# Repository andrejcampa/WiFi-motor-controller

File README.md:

# Wifi motor controller

WiFi motor controller is a highly efficient DC motor controller for creating simple remote controlled toys using a mobile device. The main purpose of the project was to build a simple WiFi controller for N/HO scale trains. However, the motor driver is not limited to trains but can also be efficiently implemented to other simple DIY toys.  The project is divided into three independent and customizable parts: hardware (HW) part, software (SW) part and optional custom 3D printed train. 

Key Specifications:
-	Supply voltage 6-15V (polarity insensitive)
-	Maximum output current 0.5A (BD622OF)/ 1A (BDF6221F)
-	Access point to the device (independent to mobile device system), no external software needed to control the device

 # Contents

- [1. HW Part](#1-hw-part) 
- [2. SW Part](#2-sw-part)
- [3. 3D Printed parts](#3-3d-printed-parts)
- [4. Support](#4-support)

## 1. HW Part

Fig 1.1: The picture of the front and back of the WiFi motor control with dimensions in mm.

The hardware of the controller was created with KiCad EDA; I have been using nightly builds release 5, since it is a huge step forward with features, libraries, etc. There are some inconsistencies between the Linux and Windows version thus you might need to make some slight changes to the naming of parts (for instance in windows the library symbol for a resistor is device:R while in Linux Device:R).
The hardware is based around BD622XF H-bridge driver and the most important features of HW are summarized in the block diagram. The maximal pulse voltage at the motor is equal to the input voltage reduced by the diode bridge voltage drop (~0.5V). Please consider using the power supply voltage of 12V - 15V to maximize the performance of H-bridge, since the module is very small 13.5 mm x 23.8 mm (31 mm) and the current capacity is limited.

Fig. 1.2: Block diagram of the module.

### Interface pins definition and connection

Fig. 1.3: Definition of pins and “connection scheme”.

Pin name | Description
------------ | -------------
**ext C (- +)** | optional external capacitor, beware of the polarity!
**LEDs** | two connections for LEDs, the maximal current is 10 mA limited by 1k resistor, this is FET driven output connected to high voltage Uin and can be used for signaling. Also marked as out 1 and out 2 in the block diagram.
**Motor_DC** | the output for DC motor, polarity and PWM voltage signal is controlled by MUC.
**U 6V-15V** | main input power for the HW and motor, Uin = 6V-15V

### PCB
The latest Gerber for PCB production can be found in the directory HW/gerber/vlak.zip. The compressed archive was already used and sent to one of the cheap Chinese PCB Manufacturer. Please contact me if you need some additional information or how to reduce the costs of a prototype.

## 2. SW part

### Flashing

The main WiFi + MCU unit is based on a small esp8285 module, ESP-M2 (doit.am). Please refer to documentation how to flash the module. You have the option to program the ESP module on the board. However, you have to supply the power to the input pins and additionally solder the ground, Rx and Tx pin directly to the module (see ESP-M2 documentation).  To flash you will need to short and hold flash pads and in the meantime short the reset pads, Figure 2.1. Flash and Reset pads are exposed on the front side of PCB.

Fig. 2.1: Exposed pads for flashing the module.

### Program
The program is written in Arduino IDE, using the open libraries, Arduino core for ESP8266 Wifi chip. To improve the response time I have used an asynchronous web server. The soft access point (SoftAP) is implemented. The program uses for SSID SRS and the serial number (SRS xxxx), the default password is SRS12345 and is for now only changeable from the program. The default page is packed in the header file as the stream of characters (string), so no file system is needed.
To access and to control the module you have to open the web browser after connecting to the hotspot. In the browser you should write the address 192.168.4.1 to access the control panel, Fig 2.2. With the slide bar you can adjust the speed, with the left and right button you can control the direction while the X button will stop the motor. In all cases soft acceleration is adapted to stabilize the module and motor, to have smooth driving experience. On the right side, the two additional buttons for turning LEDs on and off are presented. The program is written for N and HO scale train purposes and can be easily adjusted for other needs by modifying the existing page and program.

Fig. 2.2: Screenshot of UI.

## 3. 3D printed parts
The first 3-D printed locomotive is in directory 3D. You need FreeCAD to open and edit the locomotive hull. The completed locomotive can be seen in the [demonstration video](https://youtu.be/si7zXm7mwlY).

To use the WiFi module with the 3D printed hull you also need Tomytec TM-07R Motorized Chassis (N scale). By connecting the LEDs (3 mm size) and module like in Fig. 1.3 you should get a connection similar as shown in Fig. 3.1. For this project you can use very thin wires 0.05mm2 (30AWG) since the current capacity of such wire is enough for our 0.5A or 1A maximal current.

Fig. 3.1: Assembling the module into the 3D printed hull.

Please contact me if the detailed step by step instructions are needed!

## 4. Support
You are encouraged to support the project in many different ways
1. To track bugs.
2. To improve the SW part with a better response.
3. To create custom control panels in HTML.
4. To develop new 3-D printable locomotives on different chassis.
5. To make different toys using the module.
6. ***And last and maybe also very important to support the project by donating the money. The development of the HW part and printable toys take not only the time but also other resources, I have to buy (PCB, electronic components, filament,…). Unfortunately, I have the very limited amount of the own funds for a project, to speed up the development process please think about the donation. With the additional funds, even higher integration could be achieved (especially replacing the ESP module, with custom PCB antenna and ESP8285 SOC).***
7. To reduce the costs of creating a module by yourself we could make a campaign for professional assembly, but the production should be around 100 pieces or more.
8. For testing purposes (very limited amount of pieces) and for the compensation of the costs, I am willing to hand solder a few modules.

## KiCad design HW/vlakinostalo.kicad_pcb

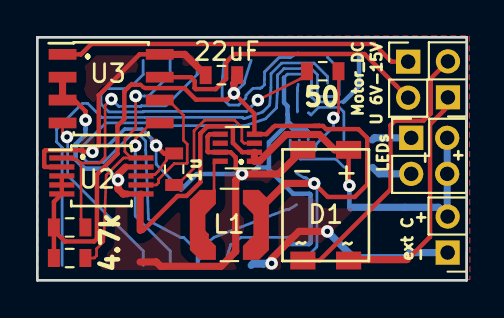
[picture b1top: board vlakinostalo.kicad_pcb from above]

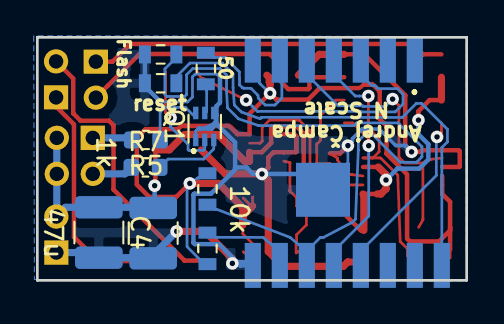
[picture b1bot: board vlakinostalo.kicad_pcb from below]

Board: 2 copper layers, 23.8 x 13.5 mm, 25 parts (11 on the bottom side), 25 nets.

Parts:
C1: 22uF; C_0603_1608Metric
C2: 1u; C_0603_1608Metric
C3, C4: 47u; C_1210_3225Metric
D1: D_Bridge_+AA-; HD_bridge_bourns
J1: ext C; PinHeader_1x02_P2.00mm_Vertical
J2: U 6V-15V; PinHeader_1x02_P2.00mm_Vertical
J3: LEDs; PinHeader_2x02_P2.00mm_Vertical
L1: L; L_Coilcraft_LPS4018
M1: Motor_DC; PinHeader_1x02_P2.00mm_Vertical
P1: ESP-M1&M2; ESP-M2
Q1: FDG1024NZ; SOT-563
R1, R2: 10k; R_0603_1608Metric
R3, R4: 4.7k; R_0603_1608Metric
R5, R7: 1k; R_0603_1608Metric
R6, R8: 50; R_0603_1608Metric
SW1: reset; R_0603_1608Metric
SW2: Flash; R_0603_1608Metric
U1: MAX15062A; DFN-8_2x2mm_P0.5mm
U2: DS3501U; MSOP-10_3x3mm_P0.5mm
U3: BD6220F; SOIC-8_3.9x4.9mm_P1.27mm

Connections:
+3V3: C1.1, L1.2, P1.7, R1.2, R2.2, R3.1, R4.1, U1.4, U2.3, U2.4, U2.5
+12V: C3.1, C4.1, D1.1, J1.2, J3.2, J3.4, U1.1, U1.2, U2.6, U2.9, U3.2, U3.3
Fin: P1.12, U3.4
GND: C1.2, C2.2, C3.2, C4.2, D1.4, J1.1, P1.8, Q1.1, Q1.4, SW1.2, SW2.2, U1.5, U1.7, U2.2, U2.8, U3.8
unnamed: C2.1, U1.3
unnamed: D1.2, J2.1
unnamed: D1.3, J2.2
unnamed: J3.1, R5.2
unnamed: J3.3, R7.1
unnamed: L1.1, U1.8
unnamed: M1.1, U3.1
unnamed: M1.2, U3.7
unnamed: P1.3, R6.2
unnamed: P1.6, R8.2
unnamed: P1.9, R1.1
unnamed: P1.10, R2.1, SW2.1
unnamed: P1.15, SW1.1
unnamed: Q1.2, R6.1
unnamed: Q1.3, R7.2
unnamed: Q1.5, R8.1
unnamed: Q1.6, R5.1
unnamed: U2.7, U3.6
Rin: P1.11, U3.5
SCL: P1.4, R4.2, U2.10
SDA: P1.5, R3.2, U2.1

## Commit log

2018-07-17 SW part initial commit
2018-07-17 Initial HW commit
2018-07-18 initial documentation
2018-07-18 correcting links
2018-07-20 Update README.md
    minor grammar updates
2018-08-03 first 3D printed body
    3D printable body for Tomytec TM-07R Motorized Chassis.
2018-08-07 connection figure
2018-08-07 added new sections
